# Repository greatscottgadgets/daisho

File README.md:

Daisho
======

Daisho is a SuperSpeed USB 3.0 FPGA platform.  The Daisho Platform is intended
for operation as a pair of components:

A mainboard with an FPGA can connect to a back-end computer via SuperSpeed USB.

A front-end board for a particular application connects to the mainboard via a
high speed parallel connector.

Front-end boards are planned that enable in-line monitoring and injection for
high speed wired communication media.

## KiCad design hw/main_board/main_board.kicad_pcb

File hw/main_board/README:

Copyright (c) 2013 Jared Boone, ShareBrained Technology, Inc.

These files are part of Daisho.

License
=======

This is a free hardware design; you can redistribute it and/or modify
it under the terms of the GNU General Public License as published by
the Free Software Foundation; either version 2, or (at your option)
any later version.

This design is distributed in the hope that it will be useful,
but WITHOUT ANY WARRANTY; without even the implied warranty of
MERCHANTABILITY or FITNESS FOR A PARTICULAR PURPOSE.  See the
GNU General Public License for more details.

You should have received a copy of the GNU General Public License
along with this design; see the file COPYING.  If not, write to
the Free Software Foundation, Inc., 51 Franklin Street,
Boston, MA 02110-1301, USA.

Hardware Notes
==============

Schematic and layout files were designed in KiCad (release 2012-05-21
bzr 3261 -stable), an open source electronic design automation package.

Order and type of copper layers:
    1_top: signal, front ("component" side, where most components are mounted)
    2_gnd: ground plane
    3_inner: signal
    4_gnd: ground plane
    5_pwr: power plane
    6_inner: signal
    7_gnd: ground plane
    8_bot: signal, back

PCB description: 8 layer PCB, 60 mil +/- 5% thickness
    LPI mask          0.4 mil
    Plating           1.2 mil   1.0 oz
    Copper      1     0.7 mil   0.5 oz
    Dielectric  1-2   4.4 mil   prepreg, 2 x 106-FR4 370
    Copper      2     1.2 mil   1.0 oz
    Dielectric  2-3   8.0 mil   core, FR4 370
    Copper      3     1.2 mil   1.0 oz
    Dielectric  3-4   7.8 mil   prepreg, 3 x 1080-FR4 370
    Copper      4     1.2 mil   1.0 oz
    Dielectric  4-5   8.0 mil   core, FR4 370
    Copper      5     1.2 mil   1.0 oz
    Dielectric  5-6   7.8 mil   prepreg, 3 x 1080-FR4 370
    Copper      6     1.2 mil   1.0 oz
    Dielectric  6-7   8.0 mil   core, FR4 370
    Copper      7     1.2 mil   1.0 oz
    Dielectric  7-8   4.4 mil   prepreg, 2 x 106-FR4 370
    Copper      8     0.7 mil   0.5 oz
    Plating           1.2 mil   1.0 oz
    LPI mask          0.4 mil

Impedance goals:
    50 Ohm +/- 10% microstrip, layers 1:2 at 7.0 mil (0.178 mm) width
    50 Ohm +/- 10% offset stripline, layers 3:2 at 6.5 mil (0.165 mm) width
    50 Ohm +/- 10% offset stripline, layers 6:7 at 6.5 mil (0.165 mm) width
    50 Ohm +/- 10% microstrip, layers 8:7 at 7.0 mil (0.178 mm) width

Soldermask
==========
Double side solder mask green
    +/- 5 mil solder mask registration

Silkscreen
==========
Double side silkscreen white
    6 mil silkscreen minimum width
    Silkscreen must be clipped by soldermask

Traces
======
5 mil (0.127 mm) min trace width
5 mil (0.127 mm) min trace isolation

Vias
====
8 mil (0.2032 mm) min via drill
17.7 mil (0.45 mm) min via pad
    4.85 mil min annular ring

Via-in-pad used in many places

Vias in pads need to be filled for assembly
    Most vias in pads are in capacitor footprints near the 780-BGA and 175-BGA

Drills
======
Drills are specified in two files:
    main_board.drl contains plated drills.
    main_board-NPTH.drl contains non-plated drills.

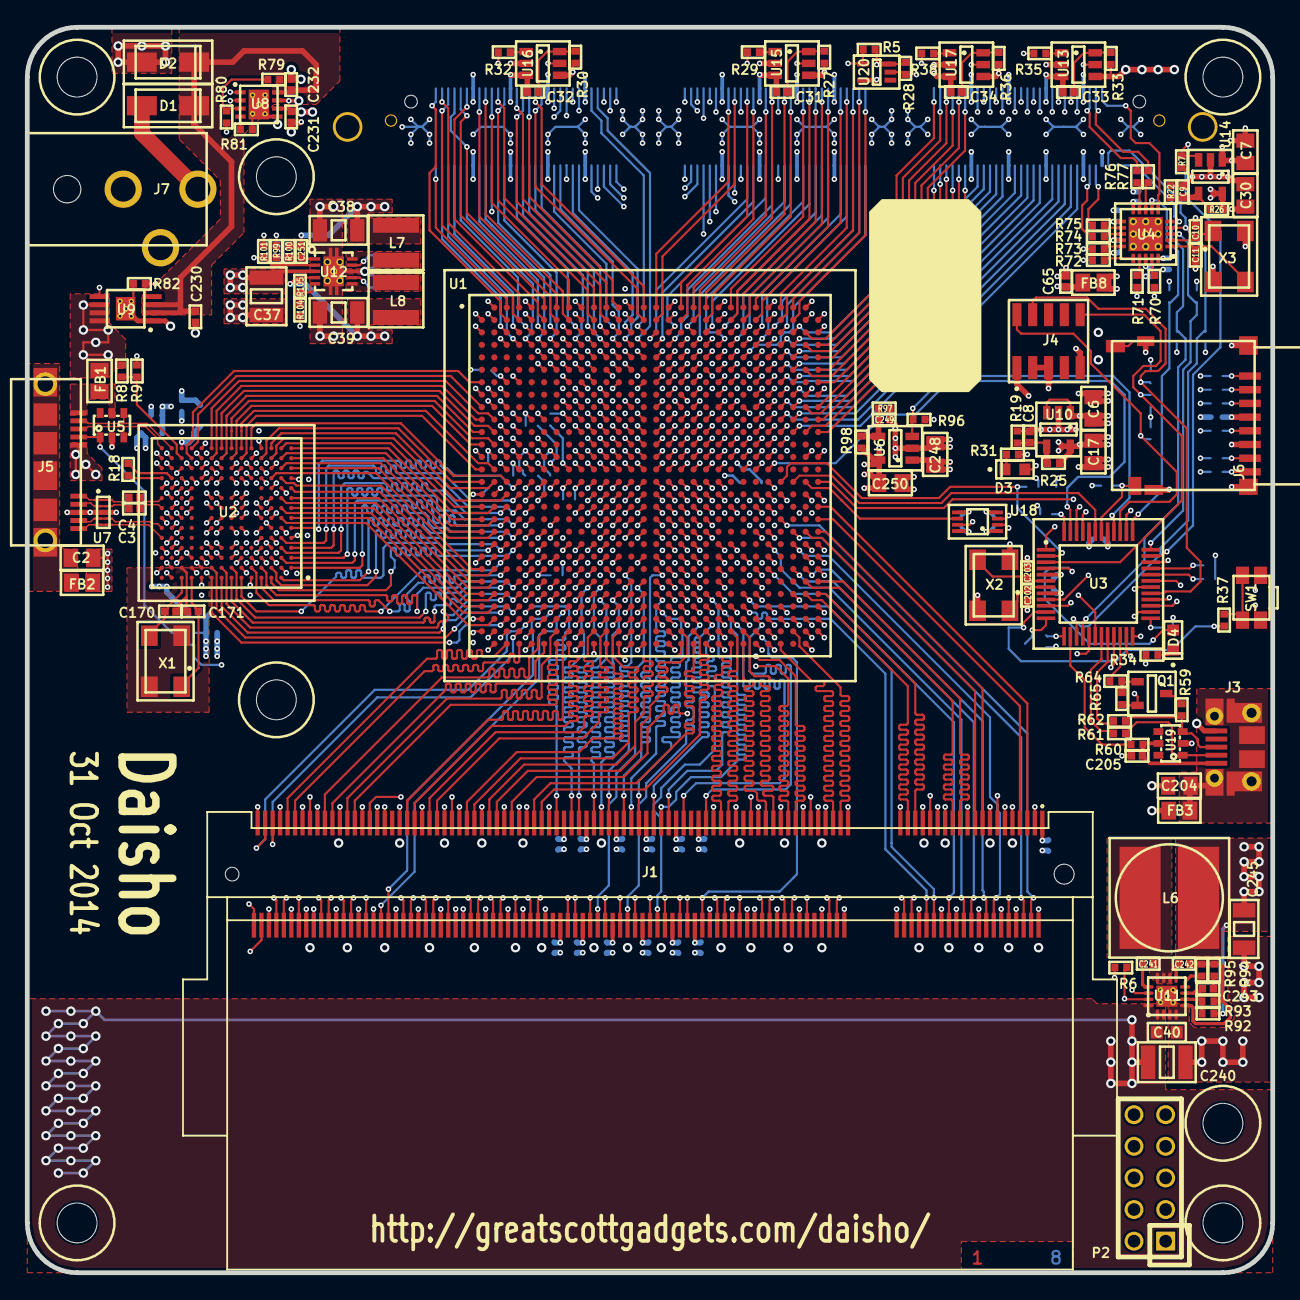
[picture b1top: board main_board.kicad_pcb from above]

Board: 8 copper layers, 100.0 x 100.0 mm, 392 parts (0 on the bottom side), 487 nets.

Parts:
C1: 1U; IPC_CAPC1005X55N
C2, C204: 10N; IPC_CAPC2012X140N
C3, C4, C5, C12, C13, C14, C15, C16, C18, C19, C20, C21, C22, C23, C24, C25, C26, C27, C28, C29, C31, C32, C33, C34, C35, C36, C41, C42, C43, C44, C45, C46, C47, C48, C49, C50, C51, C52, C53, C54, C55, C56, C57, C58, C59, C60, C61, C62, C63, C64, C65, C71, C72, C73, C74, C75, C76, C77, C78, C79, C81, C82, C83, C84, C85, C86, C87, C88, C89, C90, C91, C92, C93, C94, C95, C101, C102, C103, C104, C105, C106, C107, C108, C109, C110, C111, C112, C113, C114, C115, C116, C121, C122, C123, C124, C125, C126, C127, C128, C129, C130, C131, C132, C133, C134, C135, C141, C142, C143, C144, C145, C146, C147, C148, C149, C150, C151, C152, C153, C154, C155, C156, C160, C161, C162, C180, C181, C182, C183, C184, C185, C200, C201, C210, C211, C212, C213, C214, C215, C216, C217, C218, C219, C220, C221, C222, C230, C231, C232, C241, C4001, C4002, C4003, C4004, C4005, C4006, C4007, C4008, C4009, C4010, C4011, C4012, C4013, C4014, C4015, C4016, C4017, C4018, C4019, C4020, C4021, C4022, C4023, C4024, C4025, C4026, C4027, C4028, C4029, C4030, C4031, C4032, C4033, C4034, C4035, C4036, C4037, C4038, C4039, C4040, C4041, C4042, C4043, C4044, C4045, C4046, C4047, C4048, C4049, C4050, C4060, C4061, C4062, C4063, C4064, C4065, C4066, C4067: 100N; IPC_CAPC1005X55N
C6, C7, C17, C30, C248, C250: 10U; IPC_CAPC2012X140N
C8, C9: DNI; IPC_CAPC1005X55N
C10, C11: DNP; IPC_CAPC1005X55N
C37, C240: 22U; IPC_CAPC3225X270N
C38, C39, C245: 22U; IPC_CAPC3216X180N
C40: 100N; IPC_CAPC1608X90N
C170, C171: 27P; IPC_CAPC1005X55N
C202, C203, C251: 33P; IPC_CAPC1005X55N
C205, C242: 10N; IPC_CAPC1005X55N
C243: 2N2; IPC_CAPC1005X55N
C249: 470P; IPC_CAPC1005X55N
D1, D2: DIODESCH; IPC_DIOM5226X203N
D3, D4: LED; IPC_LEDC1608X60N
FB1, FB2, FB3, FB4, FB5, FB6, FB7, FB8: FILTER; IPC_INDC2012X130N
H1, H2, H4, H5, H6, H7, H8: HOLE; GSG-HOLE126MIL
J1: DDR2_SDRAM_SODIMM; TE_1473005-4
J2: SAMTEC_QTH-090-D; SAMTEC_QTH-090-01-F-D-A
J3: GSG-USB-MICRO-B-SHIELD; GSG-USB-MICROB-FCI-10103594
J4: CONN_5X2; SULLINS_GRPB052VWQS
J5: USB3_MICRO_AB
J6: HIROSE_DM3D
J7: BARREL_JACK; CUI_PJ-102[AB]H
L6: 2N2; TDK_VLP8040
L7, L8: 4U7; GSG-NRG4026
P1, P3: CONN_1; GSG-TESTPOINT-50MIL
P2: CONN_5X2; GSG-HEADER-2x5
Q1: BC857; IPC_SOT95P230X110-3N
R1, R2, R3, R4, R10, R11: 49R9; IPC_RESC1005X40N
R5, R7, R9, R15, R16, R17, R18, R27, R30, R33, R36, R40, R43, R44, R45, R46, R47, R48, R50, R51, R52, R53, R54, R55, R78, R82, R83, R96, R101, R102, R103: 10K; IPC_RESC1005X40N
R6, R91, R106, R107, R108, R109, R110, R111, R112: 47K; IPC_RESC1005X40N
R8: 90K9; IPC_RESC1005X40N
R12, R13, R20, R21, R23, R24, R39, R41: 1K00; IPC_RESC1005X40N
R14: 4K7; IPC_RESC1005X40N
R19, R22: 174K; IPC_RESC1005X40N
R25, R26, R98: 105K; IPC_RESC1005X40N
R28, R65: 24K; IPC_RESC1005X40N
R29, R32, R35, R37, R38, R49, R57, R58: 1K; IPC_RESC1005X40N
R31, R34: 470R; IPC_RESC1005X40N
R42: 1K0; IPC_RESC1005X40N
R59: 1K5; IPC_RESC1005X40N
R60: 100R; IPC_RESC1005X40N
R61, R62: 33R; IPC_RESC1005X40N
R64: 3K; IPC_RESC1005X40N
R70, R71, R72, R73, R74, R75, R76, R77: 10R; IPC_RESC1005X40N
R79: 47K0; IPC_RESC1005X40N
R80, R93: 10K0; IPC_RESC1005X40N
R81: 249R; IPC_RESC1005X40N
R92: 12K7; IPC_RESC1005X40N
R94: 6K34; IPC_RESC1005X40N
R95: 158K; IPC_RESC1005X40N
R97: 107K; IPC_RESC1005X40N
R99, R100: 100K; IPC_RESC1005X40N
R104: 165K; IPC_RESC1005X40N
R105: 137K; IPC_RESC1005X40N
SW1: SW_PUSH; PANASONIC_EVQP7_A_C_J_L
U1: EP4CE30F29; IPC_BGA780C100P28X28_2900X2900X350
U2: TUSB1310A; IPC_BGA175C80P14X14_1200X1200X140
U3: LPC11U1X; IPC_QFP50P900X900X160-48N
U4: SI5351C-B; IPC_QFN50P400X400X90-21L
U5, U19: GSG-IP4220CZ6; GSG-SOT457
U6, U10, U14: MIC5207YM5; IPC_SOT95P280X110-5N
U7: USB3_ESD_SON50-10
U8: TPS2113A; TI_DRB_S-PVSON-N8
U9: TPS2065C-2; TI_DGN_S-PDSO-G8
U11: TPS54218; TI_RTE_S-PWQFN-N16
U12: TPS62420; TI_DRC_S-PVSON-N10
U13, U15, U16, U17: TPS27081A; IPC_SOT95P280X110-6N
U18: 74LVC2T45; IPC_SOP50P310X100-8N
U20: INV1; IPC_SOT65P210X110-5N
X1: 40M; IPC_OSCCC320X500X105-4N
X2: 12M; IPC_OSCCC320X500X105-4N
X3: 25M; IPC_OSCCC320X500X105-4N

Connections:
/clock_generator/CLOCKGEN_INTR#: R14.2, U3.36, U4.3
/clock_generator/CLOCKGEN_OEB#: R15.2, U3.37, U4.7
/clock_generator/FE_CLKSRC: J2.5, U4.6
/clock_generator/FE_CLK_N0: J2.10, R74.2
/clock_generator/FE_CLK_N1: J2.9, R76.2
/clock_generator/FE_CLK_P0: J2.8, R75.2
/clock_generator/FE_CLK_P1: J2.7, R77.2
/clock_generator/V1P8A: C14.1, C15.1, FB8.2, U4.14, U4.18
/ddr2/A0: J1.102, U1.AE13
/ddr2/A1: J1.101, U1.AB15
/ddr2/A2: J1.100, U1.AF18
/ddr2/A3: J1.99, U1.AD15
/ddr2/A4: J1.98, U1.AF14
/ddr2/A5: J1.97, U1.AE15
/ddr2/A6: J1.94, U1.AE14
/ddr2/A7: J1.92, U1.AG19
/ddr2/A8: J1.93, U1.AF19
/ddr2/A9: J1.91, U1.AE20
/ddr2/A10: J1.105, U1.AB13
/ddr2/A11: J1.90, U1.AD14
/ddr2/A12: J1.89, U1.AD19
/ddr2/A13: J1.116, U1.AH10
/ddr2/A14: J1.86, U1.AC17
/ddr2/A15: J1.84, U1.AE16
/ddr2/BA0: J1.107, U1.AD12
/ddr2/BA1: J1.106, U1.AH12
/ddr2/BA2: J1.85, U1.AF21
/ddr2/CAS#: J1.113, U1.AC11
/ddr2/CK0: J1.30, U1.AD22
/ddr2/CK1: J1.164, U1.AE7
/ddr2/CK#0: J1.32, U1.AE22
/ddr2/CK#1: J1.166, U1.AE8
/ddr2/CKE0: J1.79, U1.AF23
/ddr2/CKE1: J1.80, U1.AG23
/ddr2/DM0: J1.10, U1.AB28
/ddr2/DM1: J1.26, U1.AB24
/ddr2/DM2: J1.52, U1.AF25
/ddr2/DM3: J1.67, U1.AH19
/ddr2/DM4: J1.130, U1.AC15
/ddr2/DM5: J1.147, U1.AF8
/ddr2/DM6: J1.170, U1.AB9
/ddr2/DM7: J1.185, U1.AE6
/ddr2/DQ0: J1.5, U1.U28
/ddr2/DQ1: J1.7, U1.V28
/ddr2/DQ2: J1.17, U1.W28
/ddr2/DQ3: J1.19, U1.W27
/ddr2/DQ4: J1.4, U1.V25
/ddr2/DQ5: J1.6, U1.W26
/ddr2/DQ6: J1.14, U1.Y26
/ddr2/DQ7: J1.16, U1.AB27
/ddr2/DQ8: J1.23, U1.AC28
/ddr2/DQ9: J1.25, U1.AC27
/ddr2/DQ10: J1.35, U1.AD28
/ddr2/DQ11: J1.37, U1.AD27
/ddr2/DQ12: J1.20, U1.AB26
/ddr2/DQ13: J1.22, U1.Y24
/ddr2/DQ14: J1.36, U1.AD26
/ddr2/DQ15: J1.38, U1.AE28
/ddr2/DQ16: J1.43, U1.AG26
/ddr2/DQ17: J1.45, U1.AH25
/ddr2/DQ18: J1.55, U1.AF22
/ddr2/DQ19: J1.57, U1.AE21
/ddr2/DQ20: J1.44, U1.AE25
/ddr2/DQ21: J1.46, U1.AE24
/ddr2/DQ22: J1.56, U1.AF20
/ddr2/DQ23: J1.58, U1.AD18
/ddr2/DQ24: J1.61, U1.AG22
/ddr2/DQ25: J1.63, U1.AH22
/ddr2/DQ26: J1.73, U1.AG21
/ddr2/DQ27: J1.75, U1.AH21
/ddr2/DQ28: J1.62, U1.AF24
/ddr2/DQ29: J1.64, U1.AH23
/ddr2/DQ30: J1.74, U1.AE19
/ddr2/DQ31: J1.76, U1.AD17
/ddr2/DQ32: J1.123, U1.AG18
/ddr2/DQ33: J1.125, U1.AH18
/ddr2/DQ34: J1.135, U1.AG17
/ddr2/DQ35: J1.137, U1.AH17
/ddr2/DQ36: J1.124, U1.AE17
/ddr2/DQ37: J1.126, U1.AF16
/ddr2/DQ38: J1.134, U1.AF15
/ddr2/DQ39: J1.136, U1.AB16
/ddr2/DQ40: J1.141, U1.AG12
/ddr2/DQ41: J1.143, U1.AH11
/ddr2/DQ42: J1.151, U1.AG11
/ddr2/DQ43: J1.153, U1.AG10
/ddr2/DQ44: J1.140, U1.AE12
/ddr2/DQ45: J1.142, U1.AE11
/ddr2/DQ46: J1.152, U1.AE9
/ddr2/DQ47: J1.154, U1.AF10
/ddr2/DQ48: J1.157, U1.AH8
/ddr2/DQ49: J1.159, U1.AG8
/ddr2/DQ50: J1.173, U1.AH7
/ddr2/DQ51: J1.175, U1.AG7
/ddr2/DQ52: J1.158, U1.AF9
/ddr2/DQ53: J1.160, U1.AD10
/ddr2/DQ54: J1.174, U1.AC8
/ddr2/DQ55: J1.176, U1.AF7
/ddr2/DQ56: J1.179, U1.AH6
/ddr2/DQ57: J1.181, U1.AG6
/ddr2/DQ58: J1.189, U1.AH4
/ddr2/DQ59: J1.191, U1.AH3
/ddr2/DQ60: J1.180, U1.AD8
/ddr2/DQ61: J1.182, U1.AF6
/ddr2/DQ62: J1.192, U1.AF4
/ddr2/DQ63: J1.194, U1.AG3
/ddr2/DQS0: J1.13, U1.T25
/ddr2/DQS1: J1.31, U1.AF27
/ddr2/DQS2: J1.51, U1.AF26
/ddr2/DQS3: J1.70, U1.AE18
/ddr2/DQS4: J1.131, U1.AF17
/ddr2/DQS5: J1.148, U1.AF11
/ddr2/DQS6: J1.169, U1.AE10
/ddr2/DQS7: J1.188, U1.AD7
/ddr2/ODT0: J1.114, U1.AF12
/ddr2/ODT1: J1.119, U1.AE5
/ddr2/RAS#: J1.108, U1.AC14
/ddr2/S#0: J1.110, U1.AF13
/ddr2/S#1: J1.115, U1.AC10
/ddr2/VREF: C180.2, C181.1, C182.2, C183.1, C184.2, C185.1, C222.1, J1.1, R20.2, R21.1, U1.AA12, U1.AA14, U1.AA15, U1.AA24, U1.AB11, U1.AB20, U1.AC18, U1.R24, U1.U23, U1.U24, U1.Y10, U1.Y17
/ddr2/WE#: J1.109, U1.AD11
/fpga_configuration/DATA0: R47.1, U1.N7
/fpga_configuration/DCLK: R46.1, U1.P3
/fpga_configuration/FPGA_NSTATUS: R50.2, U1.M6, U3.48
/fpga_configuration/FPGA_TCK: P2.1, R49.1, U1.P5, U3.13
/fpga_configuration/FPGA_TDI: P2.9, R44.2, U1.P7, U3.17
/fpga_configuration/FPGA_TDO_V1P8: U1.P6, U18.7
/fpga_configuration/FPGA_TMS: P2.5, R45.2, U1.P8, U3.18
/fpga_configuration/NCE: R48.1, U1.R8
/fpga_configuration/NCONFIG: R43.2, U1.P4
/fpga_configuration/PIPE_RATE: U1.N3, U2.L6
/fpga_configuration/PIPE_TX_DETRX_LPBK: U1.K4, U2.M6
/fpga_configuration/PIPE_TX_ELECIDLE: U1.M4, U2.K3
/fpga_configuration/PIPE_TX_MARGIN0: U1.K3, U2.M9
/fpga_configuration/PIPE_TX_MARGIN1: U1.H3, U2.M10
/fpga_configuration/PIPE_TX_MARGIN2: U1.G4, U2.M11
/fpga_configuration/PIPE_TX_ONESZEROS: U1.M3, U2.M4
/fpga_configuration/PIPE_TX_SWING: U1.L4, U2.M5
/fpga_configuration/ULPI_CLK: U1.J1, U2.P11
/fpga_configuration/ULPI_DATA0: U1.K1, U2.N9
/fpga_configuration/ULPI_DATA1: U1.K2, U2.P9
/fpga_configuration/ULPI_DATA2: U1.L2, U2.P8
/fpga_configuration/ULPI_DATA3: U1.L1, U2.N8
/fpga_configuration/ULPI_DATA4: U1.M2, U2.P7
/fpga_configuration/ULPI_DATA5: U1.M1, U2.N7
/fpga_configuration/ULPI_DATA6: U1.P2, U2.P6
/fpga_configuration/ULPI_DATA7: U1.P1, U2.N6
/fpga_configuration/ULPI_DIR: U1.L3, U2.M7
/fpga_configuration/ULPI_NXT: U1.G1, U2.N11
/fpga_configuration/ULPI_STP: U1.J3, U2.M8
/fpga_ddr2/CLK_N0: R72.2, U1.AH14
/fpga_ddr2/CLK_N1: R70.2, U1.Y28
/fpga_ddr2/CLK_P0: R73.2, U1.AG14
/fpga_ddr2/CLK_P1: R71.2, U1.Y27
/fpga_ddr2/SPI_MISO_V1P8: U1.R27, U18.6
/fpga_ddr2/SPI_MOSI: U1.R28, U3.38
/fpga_ddr2/SPI_SCK: U1.R26, U3.43
/fpga_ddr2/SPI_SS: R52.2, U1.R25, U3.2
/fpga_front_end_bank_b/D0: J2.62, U1.E22
/fpga_front_end_bank_b/D1: J2.61, U1.B26
/fpga_front_end_bank_b/D2: J2.64, U1.C25
/fpga_front_end_bank_b/D3: J2.63, U1.A26
/fpga_front_end_bank_b/D4: J2.66, U1.C24
/fpga_front_end_bank_b/D5: J2.65, U1.B25
/fpga_front_end_bank_b/D6: J2.68, U1.D23
/fpga_front_end_bank_b/D7: J2.67, U1.A25
/fpga_front_end_bank_b/D8: J2.70, U1.C23
/fpga_front_end_bank_b/D9: J2.69, U1.B23
/fpga_front_end_bank_b/D10: J2.74, U1.C22
/fpga_front_end_bank_b/D11: J2.73, U1.A23
/fpga_front_end_bank_b/D12: J2.76, U1.D21
/fpga_front_end_bank_b/D13: J2.75, U1.B22
/fpga_front_end_bank_b/D14: J2.78, U1.C20
/fpga_front_end_bank_b/D15: J2.77, U1.A22
/fpga_front_end_bank_b/D16: J2.80, U1.C19
/fpga_front_end_bank_b/D17: J2.79, U1.B21
/fpga_front_end_bank_b/D18: J2.82, U1.D20
/fpga_front_end_bank_b/D19: J2.81, U1.A21
/fpga_front_end_bank_b/D20: J2.86, U1.D18
/fpga_front_end_bank_b/D21: J2.85, U1.B19
/fpga_front_end_bank_b/D22: J2.88, U1.C18
/fpga_front_end_bank_b/D23: J2.87, U1.A19
/fpga_front_end_bank_b/D24: J2.90, U1.G21
/fpga_front_end_bank_b/D25: J2.89, U1.D22
/fpga_front_end_bank_b/D26: J2.92, U1.D16
/fpga_front_end_bank_b/D27: J2.91, U1.B18
/fpga_front_end_bank_b/D28: J2.94, U1.C16
/fpga_front_end_bank_b/D29: J2.93, U1.A18
/fpga_front_end_bank_b/D30: J2.98, U1.D15
/fpga_front_end_bank_b/D31: J2.97, U1.B17
/fpga_front_end_bank_b/D32: J2.100, U1.C15
/fpga_front_end_bank_b/D33: J2.99, U1.A17
/fpga_front_end_bank_b/D34: J2.102, U1.G20
/fpga_front_end_bank_b/D35: J2.101, U1.E18
/fpga_front_end_bank_b/D36: J2.104, U1.D19
/fpga_front_end_bank_b/D37: J2.103, U1.B15
/fpga_front_end_bank_b/D38: J2.106, U1.C21
/fpga_front_end_bank_b/D39: J2.105, U1.A15
/fpga_front_end_bank_b/D40: J2.110, U1.F21
/fpga_front_end_bank_b/D41: J2.109, U1.D17
/fpga_front_end_bank_b/D42: J2.112, U1.E21
/fpga_front_end_bank_b/D43: J2.111, U1.F17
/fpga_front_end_bank_b/D44: J2.114, U1.H17
/fpga_front_end_bank_b/D45: J2.113, U1.G18
/fpga_front_end_bank_b/D46: J2.116, U1.H16
/fpga_front_end_bank_b/D47: J2.115, U1.F15
/fpga_front_end_bank_b/D48: J2.118, U1.J17
/fpga_front_end_bank_b/D49: J2.117, U1.G16
/fpga_front_end_bank_b/D50: J2.120, U1.E17
/fpga_front_end_bank_b/D51: J2.119, U1.E15
/fpga_front_end_bank_b/VCCIO_DEFAULT_EN: R5.1, U15.5, U16.5, U17.5, U20.4
/fpga_front_end_bank_b/VREF: C19.2, C23.1, R12.1, R13.2, U1.F18, U1.F22, U1.G15, U1.G17
/fpga_front_end_bank_c/D0: J2.122, U1.E8
/fpga_front_end_bank_c/D1: J2.121, U1.F12
/fpga_front_end_bank_c/D2: J2.124, U1.E11
/fpga_front_end_bank_c/D3: J2.123, U1.E12
/fpga_front_end_bank_c/D4: J2.126, U1.E14
/fpga_front_end_bank_c/D5: J2.125, U1.C8
/fpga_front_end_bank_c/D6: J2.128, U1.E7
/fpga_front_end_bank_c/D7: J2.127, U1.D14
/fpga_front_end_bank_c/D8: J2.130, U1.E10
/fpga_front_end_bank_c/D9: J2.129, U1.C14
/fpga_front_end_bank_c/D10: J2.134, U1.D13
/fpga_front_end_bank_c/D11: J2.133, U1.F10
/fpga_front_end_bank_c/D12: J2.136, U1.C13
/fpga_front_end_bank_c/D13: J2.135, U1.D10
/fpga_front_end_bank_c/D14: J2.138, U1.G10
/fpga_front_end_bank_c/D15: J2.137, U1.D8
/fpga_front_end_bank_c/D16: J2.140, U1.D12
/fpga_front_end_bank_c/D17: J2.139, U1.F7
/fpga_front_end_bank_c/D18: J2.142, U1.C12
/fpga_front_end_bank_c/D19: J2.141, U1.F8
/fpga_front_end_bank_c/D20: J2.146, U1.C11
/fpga_front_end_bank_c/D21: J2.145, U1.B14
/fpga_front_end_bank_c/D22: J2.148, U1.D11
/fpga_front_end_bank_c/D23: J2.147, U1.A14
/fpga_front_end_bank_c/D24: J2.150, U1.C10
/fpga_front_end_bank_c/D25: J2.149, U1.A12
/fpga_front_end_bank_c/D26: J2.152, U1.D9
/fpga_front_end_bank_c/D27: J2.151, U1.B11
/fpga_front_end_bank_c/D28: J2.154, U1.C9
/fpga_front_end_bank_c/D29: J2.153, U1.A11
/fpga_front_end_bank_c/D30: J2.158, U1.D7
/fpga_front_end_bank_c/D31: J2.157, U1.B10
/fpga_front_end_bank_c/D32: J2.160, U1.C7
/fpga_front_end_bank_c/D33: J2.159, U1.A10
/fpga_front_end_bank_c/D34: J2.162, U1.G8
/fpga_front_end_bank_c/D35: J2.161, U1.A8
/fpga_front_end_bank_c/D36: J2.164, U1.D6
/fpga_front_end_bank_c/D37: J2.163, U1.B8
/fpga_front_end_bank_c/D38: J2.166, U1.C6
/fpga_front_end_bank_c/D39: J2.165, U1.A7
/fpga_front_end_bank_c/D40: J2.170, U1.D5
/fpga_front_end_bank_c/D41: J2.169, U1.B6
/fpga_front_end_bank_c/D42: J2.172, U1.C5
/fpga_front_end_bank_c/D43: J2.171, U1.A6
/fpga_front_end_bank_c/D44: J2.174, U1.C4
/fpga_front_end_bank_c/D45: J2.173, U1.B7
/fpga_front_end_bank_c/D46: J2.176, U1.D4
/fpga_front_end_bank_c/D47: J2.175, U1.B4
/fpga_front_end_bank_c/D48: J2.178, U1.C3
/fpga_front_end_bank_c/D49: J2.177, U1.A4
/fpga_front_end_bank_c/D50: J2.180, U1.A3
/fpga_front_end_bank_c/D51: J2.179, U1.B3
/fpga_front_end_bank_c/VREF: C20.2, C22.1, R41.2, R42.1, U1.F11, U1.G9, U1.G12, U1.G14
/fpga_front_end_misc/D0: J2.14, U1.L26
/fpga_front_end_misc/D1: J2.13, U1.M23
/fpga_front_end_misc/D2: J2.16, U1.K25
/fpga_front_end_misc/D3: J2.15, U1.L23
/fpga_front_end_misc/D4: J2.18, U1.K26
/fpga_front_end_misc/D5: J2.17, U1.J23
/fpga_front_end_misc/D6: J2.20, U1.J25
/fpga_front_end_misc/D7: J2.19, U1.H23
/fpga_front_end_misc/D8: J2.22, U1.J26
/fpga_front_end_misc/D9: J2.21, U1.G23
/fpga_front_end_misc/D10: J2.26, U1.H26
/fpga_front_end_misc/D11: J2.25, U1.M24
/fpga_front_end_misc/D12: J2.28, U1.G25
/fpga_front_end_misc/D13: J2.27, U1.L25
/fpga_front_end_misc/D14: J2.30, U1.G26
/fpga_front_end_misc/D15: J2.29, U1.L24
/fpga_front_end_misc/D16: J2.32, U1.F25
/fpga_front_end_misc/D17: J2.31, U1.J24
/fpga_front_end_misc/D18: J2.34, U1.F26
/fpga_front_end_misc/D19: J2.33, U1.H25
/fpga_front_end_misc/D20: J2.38, U1.E25
/fpga_front_end_misc/D21: J2.37, U1.H24
/fpga_front_end_misc/D22: J2.40, U1.E26
/fpga_front_end_misc/D23: J2.39, U1.G24
/fpga_front_end_misc/D24: J2.42, U1.D25
/fpga_front_end_misc/D25: J2.41, U1.F24
/fpga_front_end_misc/D26: J2.44, U1.D26
/fpga_front_end_misc/D27: J2.43, U1.E24
/fpga_front_end_misc/D28: J2.46, U1.C26
/fpga_front_end_misc/D29: J2.45, U1.D24
/fpga_front_end_misc/D30: J2.50, U1.L28
/fpga_front_end_misc/D31: J2.49, U1.F27
/fpga_front_end_misc/D32: J2.52, U1.L27
/fpga_front_end_misc/D33: J2.51, U1.F28
/fpga_front_end_misc/D34: J2.54, U1.K28
/fpga_front_end_misc/D35: J2.53, U1.E28
/fpga_front_end_misc/D36: J2.56, U1.J27
/fpga_front_end_misc/D37: J2.55, U1.D27
/fpga_front_end_misc/D38: J2.58, U1.J28
/fpga_front_end_misc/D39: J2.57, U1.D28
/fpga_front_end_misc/D40: J2.60, U1.G28
/fpga_front_end_misc/D41: J2.59, U1.C27
/fpga_front_end_misc/FPGA_CONF_DONE: R51.2, U1.P24, U3.47
/fpga_front_end_misc/VREF: C18.2, C21.1, R23.1, R24.2, U1.J22, U1.M21, U1.M25, U1.N21
/fpga_power/VCCD_PLL: C4064.1, C4065.1, C4066.1, C4067.1, FB7.2, U1.J9, U1.J20, U1.Y9, U1.Y20
/fpga_usb0/PIPE_POWERDOWN0: U1.R7, U2.H3
/fpga_usb0/PIPE_POWERDOWN1: U1.R5, U2.G3
/fpga_usb0/PIPE_PWRPRESENT: U1.AB5, U2.H11
/fpga_usb0/PIPE_RESETN: R16.2, U1.AB6, U2.J11
/fpga_usb0/PIPE_RX_DATA0: U1.T4, U2.E2
/fpga_usb0/PIPE_RX_DATA1: U1.U3, U2.D2
/fpga_usb0/PIPE_RX_DATA2: U1.U4, U2.D1
/fpga_usb0/PIPE_RX_DATA3: U1.V4, U2.C1
/fpga_usb0/PIPE_RX_DATA4: U1.V3, U2.C2
/fpga_usb0/PIPE_RX_DATA5: U1.W4, U2.B1
/fpga_usb0/PIPE_RX_DATA6: U1.W3, U2.A2
/fpga_usb0/PIPE_RX_DATA7: U1.Y4, U2.A3
/fpga_usb0/PIPE_RX_DATA8: U1.Y3, U2.B3
/fpga_usb0/PIPE_RX_DATA9: U1.AB3, U2.A4
/fpga_usb0/PIPE_RX_DATA10: U1.AC4, U2.B4
/fpga_usb0/PIPE_RX_DATA11: U1.AA3, U2.B5
/fpga_usb0/PIPE_RX_DATA12: U1.AD3, U2.B8
/fpga_usb0/PIPE_RX_DATA13: U1.AE4, U2.A8
/fpga_usb0/PIPE_RX_DATA14: U1.AF3, U2.A9
/fpga_usb0/PIPE_RX_DATA15: U1.AE3, U2.B9
/fpga_usb0/PIPE_RX_DATAK0: U1.AD4, U2.A7
/fpga_usb0/PIPE_RX_DATAK1: U1.AC3, U2.B7
/fpga_usb0/PIPE_RX_ELECIDLE: U1.R6, U2.F3
/fpga_usb0/PIPE_RX_POLARITY: U1.AC5, U2.C8
/fpga_usb0/PIPE_RX_STATUS0: U1.V7, U2.C5
/fpga_usb0/PIPE_RX_STATUS1: U1.Y6, U2.C6
/fpga_usb0/PIPE_RX_STATUS2: U1.AA6, U2.C7
/fpga_usb0/PIPE_RX_TERMINATION: U1.U5, U2.D3
/fpga_usb0/PIPE_RX_VALID: U1.R4, U2.F1
/fpga_usb0/PIPE_TX_CLK: U1.AC1, U2.K1
/fpga_usb0/PIPE_TX_DATA0: U1.R3, U2.P5
/fpga_usb0/PIPE_TX_DATA1: U1.R1, U2.N4
/fpga_usb0/PIPE_TX_DATA2: U1.R2, U2.P3
/fpga_usb0/PIPE_TX_DATA3: U1.T3, U2.N3
/fpga_usb0/PIPE_TX_DATA4: U1.U1, U2.P2
/fpga_usb0/PIPE_TX_DATA5: U1.V1, U2.N2
/fpga_usb0/PIPE_TX_DATA6: U1.U2, U2.P1
/fpga_usb0/PIPE_TX_DATA7: U1.V2, U2.N1
/fpga_usb0/PIPE_TX_DATA8: U1.W2, U2.M1
/fpga_usb0/PIPE_TX_DATA9: U1.W1, U2.M2
/fpga_usb0/PIPE_TX_DATA10: U1.AB2, U2.L2
/fpga_usb0/PIPE_TX_DATA11: U1.AB1, U2.L3
/fpga_usb0/PIPE_TX_DATA12: U1.AD1, U2.J2
/fpga_usb0/PIPE_TX_DATA13: U1.AD2, U2.H1
/fpga_usb0/PIPE_TX_DATA14: U1.AE1, U2.H2
/fpga_usb0/PIPE_TX_DATA15: U1.AF2, U2.G2
/fpga_usb0/PIPE_TX_DATAK0: U1.AC2, U2.J1
/fpga_usb0/PIPE_TX_DATAK1: U1.AE2, U2.G1
/fpga_usb0/PIPE_TX_DEEMPH0: U1.AA5, U2.L11
/fpga_usb0/PIPE_TX_DEEMPH1: U1.AA7, U2.K11
/fpga_usb0/USB3_ID: J5.4, R39.2, U5.1
/front_end/FE_EN: U3.9, U13.5
/front_end/FE_I2C_SCL: J1.197, J2.4, R57.2, U1.AF5, U3.15, U4.4
/front_end/FE_I2C_SDA: J1.195, J2.2, R58.2, U1.AG4, U3.16, U4.5
/front_end/FE_VCCIO_A: C18.1, C34.2, C90.1, C91.1, C92.1, C93.1, C94.1, C95.1, J2.12, J2.24, J2.36, J2.48, R23.2, U1.B28, U1.H28, U1.K24, U1.L21, U1.N24, U1.N28, U17.2, U17.3
/front_end/FE_VCCIO_B: C19.1, C31.2, C81.1, C82.1, C83.1, C84.1, C85.1, C86.1, C87.1, C88.1, C89.1, J2.71, J2.72, J2.83, J2.84, J2.95, J2.96, J2.107, J2.108, R10.2, R12.2, U1.A16, U1.A20, U1.A24, U1.A27, U1.E16, U1.E20, U1.E23, U1.H18, U1.J15, U15.2, U15.3
/front_end/FE_VCCIO_C: C20.1, C32.2, C71.1, C72.1, C73.1, C74.1, C75.1, C76.1, C77.1, C78.1, C79.1, J2.131, J2.132, J2.143, J2.144, J2.155, J2.156, J2.167, J2.168, R41.1, U1.A2, U1.A5, U1.A9, U1.A13, U1.E6, U1.E9, U1.E13, U1.H11, U1.J13, U16.2, U16.3
/front_end/VRAW_SW: C33.2, J2.11, J2.23, J2.35, J2.47, U13.2, U13.3
/microcontroller/ALT_SW_STAT: R78.1, U3.32, U8.1
/microcontroller/DDR2_SA0: J1.198, U3.21
/microcontroller/DDR2_SA1: J1.200, U3.23
/microcontroller/FPGA_MISO_V3P3: U3.30, U18.3
/microcontroller/FPGA_TDO_V3P3: P2.3, U3.26, U18.2
/microcontroller/LED_STATUS: D4.1, U3.4
/microcontroller/RESET#: J4.10, R54.2, U3.3
/microcontroller/RXD: P1.1, R37.1, U3.11
/microcontroller/SD_CS#: J6.2, R109.2, U3.10
/microcontroller/SD_DET: J6.A, R106.2, U3.42
/microcontroller/SD_MISO: J6.7, R107.2, U3.27
/microcontroller/SD_MOSI: J6.3, R108.2, U3.28
/microcontroller/SD_SCK: J6.5, R112.1, U3.31
/microcontroller/SWCLK: J4.4, R55.1, U3.29
/microcontroller/SWDIO: J4.2, R53.2, U3.39
/microcontroller/TXD: P3.1, U3.12
/microcontroller/USB2_SHIELD: C204.1, FB3.2, J3.6
/microcontroller/USB_POWER_EN: R82.2, U3.34, U9.4
/microcontroller/USB_POWER_FLT#: R83.1, U3.33, U9.5
/microcontroller/V1P8_PWRGD: R91.2, U3.25, U11.14
/microcontroller/V1PX_SMPS_MODE: R101.2, U3.1, U12.2
/power/V1P1_EN: R103.2, U3.45, U12.7
/power/V1P1_FB: R104.1, R105.2, U12.5
/power/V1P1_SW: L8.1, U12.6
/power/V1P2_EN: R102.2, U3.46, U12.9
/power/V1P2_FB: C251.1, R99.1, R100.2, U12.1
/power/V1P2_SW: L7.2, U12.10
/power/V1P8_EN: R6.2, U3.24, U11.15
/power/V1P8_PH: C241.2, L6.1, U11.10, U11.11, U11.12
/power/V2P5_EN: R96.2, U3.40, U6.3
/power/V3P3A_EN: R7.2, U3.35, U14.3
/power/VALT: C230.1, C232.1, D1.2, D2.2, R79.2, U8.8, U9.2, U9.3
/usb0_interfaces/DM: J5.2, U2.P13, U5.4
/usb0_interfaces/DP: J5.3, U2.P14, U5.3
/usb0_interfaces/ELAS_BUF_MODE: U1.AD5, U2.C9
/usb0_interfaces/OUT_ENABLE: R17.2, U1.G3, U2.L10
/usb0_interfaces/PCLK: U1.Y2, U2.A6
/usb0_interfaces/PHY_RESETN: U1.N4, U2.J3
/usb0_interfaces/PHY_STATUS: U1.V5, U2.E3
/usb0_interfaces/SSRXM: J5.9, U2.F14, U7.4
/usb0_interfaces/SSRXP: J5.10, U2.E14, U7.5
/usb0_interfaces/SSTXM: C4.1, U2.J14
/usb0_interfaces/SSTXM_C: C4.2, J5.6, U7.1
/usb0_interfaces/SSTXP: C3.1, U2.H14
/usb0_interfaces/SSTXP_C: C3.2, J5.7, U7.2
/usb0_interfaces/USB3_SHIELD: C2.1, FB2.2, J5.11
/usb0_interfaces/VBUS: R8.1, R9.2, U2.N12
/usb0_interfaces/VSSOSC: C170.2, C171.2, U2.B12, X1.2, X1.4
/usb0_interfaces/VUSB_RAW: FB1.1, J5.1, U5.5
/usb0_interfaces/XI: C170.1, U2.A12, X1.3
/usb0_interfaces/XO: C171.1, U2.A11, X1.1
/usb0_power/A1P1: C1.1, C145.1, C146.1, C147.1, C148.1, C149.1, C150.1, FB6.2, U2.C11, U2.C12, U2.D14, U2.G13, U2.G14, U2.K14, U2.M14
/usb0_power/A1P8: C142.1, C143.1, C144.1, FB5.2, U2.A13, U2.C10, U2.N14
/usb0_power/A3P3: C141.1, FB4.2, U2.P12
GND: C1.2, C2.2, C5.2, C6.2, C7.2, C8.2, C9.2, C10.1, C11.2, C12.2, C13.2, C14.2, C15.2, C16.2, C17.2, C21.2, C22.2, C23.2, C24.2, C25.2, C26.2, C27.2, C28.2, C29.2, C30.2, C35.1, C36.1, C37.2, C38.2, C39.1, C40.2, C41.2, C42.2, C43.2, C44.2, C45.2, C46.2, C47.2, C48.2, C49.2, C50.2, C51.2, C52.2, C53.2, C54.2, C55.2, C56.2, C57.2, C58.2, C59.2, C60.2, C61.2, C62.2, C63.2, C64.2, C65.2, C71.2, C72.2, C73.2, C74.2, C75.2, C76.2, C77.2, C78.2, C79.2, C81.2, C82.2, C83.2, C84.2, C85.2, C86.2, C87.2, C88.2, C89.2, C90.2, C91.2, C92.2, C93.2, C94.2, C95.2, C101.2, C102.2, C103.2, C104.2, C105.2, C106.2, C107.2, C108.2, C109.2, C110.2, C111.2, C112.2, C113.2, C114.2, C115.2, C116.2, C121.2, C122.2, C123.2, C124.2, C125.2, C126.2, C127.2, C128.2, C129.2, C130.2, C131.2, C132.2, C133.2, C134.2, C135.2, C141.2, C142.2, C143.2, C144.2, C145.2, C146.2, C147.2, C148.2, C149.2, C150.2, C151.2, C152.2, C153.2, C154.2, C155.2, C156.2, C160.2, C161.2, C162.2, C181.2, C183.2, C185.2, C200.2, C201.2, C202.1, C203.2, C204.2, C205.2, C210.2, C211.2, C212.2, C213.2, C214.2, C215.2, C216.2, C217.2, C218.2, C219.2, C220.2, C221.2, C222.2, C230.2, C231.2, C232.2, C240.2, C242.2, C245.2, C248.2, C249.2, C250.2, C4001.2, C4002.2, C4003.2, C4004.2, C4005.2, C4006.2, C4007.2, C4008.2, C4009.2, C4010.2, C4011.2, C4012.2, C4013.2, C4014.2, C4015.2, C4016.2, C4017.2, C4018.2, C4019.2, C4020.2, C4021.2, C4022.2, C4023.2, C4024.2, C4025.2, C4026.2, C4027.2, C4028.2, C4029.2, C4030.2, C4031.2, C4032.2, C4033.2, C4034.2, C4035.2, C4036.2, C4037.2, C4038.2, C4039.2, C4040.2, C4041.2, C4042.2, C4043.2, C4044.2, C4045.2, C4046.2, C4047.2, C4048.2, C4049.2, C4050.2, C4060.2, C4061.2, C4062.2, C4063.2, C4064.2, C4065.2, C4066.2, C4067.2, FB2.1, FB3.1, J1.2, J1.3, J1.8, J1.9, J1.11, J1.12, J1.15, J1.18, J1.21, J1.24, J1.27, J1.28, J1.29, J1.33, J1.34, J1.39, J1.40, J1.41, J1.42, J1.47, J1.48, J1.49, J1.53, J1.54, J1.59, J1.60, J1.65, J1.66, J1.68, J1.71, J1.72, J1.77, J1.78, J1.121, J1.122, J1.127, J1.128, J1.129, J1.132, J1.133, J1.138, J1.139, J1.144, J1.145, J1.146, J1.149, J1.150, J1.155, J1.156, J1.161, J1.162, J1.165, J1.167, J1.168, J1.171, J1.172, J1.177, J1.178, J1.183, J1.184, J1.186, J1.187, J1.190, J1.193, J1.196, J2.A0, J2.A1, J2.A2, J2.A3, J2.B0, J2.B1, J2.B2, J2.B3, J2.C0, J2.C1, J2.C2, J2.C3, J3.5, J4.3, J4.5, J4.9, J5.5, J5.8, J6.0, J6.6, J6.B, J7.2, P2.2, P2.10, R2.1, R4.1, R5.2, R6.1, R7.1, R9.1, R11.1, R13.1, R16.1, R17.1, R19.2, R21.2, R22.2, R24.1, R28.2, R29.2, R31.2, R32.2, R34.2, R35.2, R38.2, R42.2, R46.2, R47.2, R48.2, R49.2, R55.2, R80.2, R81.2, R82.1, R93.2, R94.2, R95.2, R96.1, R97.2, R99.2, R101.1, R102.1, R103.1, R104.2, R112.2, SW1.2, U1.AA2, U1.AA9, U1.AA20, U1.AA27, U1.AC6, U1.AC9, U1.AC13, U1.AC16, U1.AC20, U1.AC23, U1.AF1, U1.AF28, U1.AG2, U1.AG5, U1.AG9, U1.AG13, U1.AG16, U1.AG20, U1.AG24, U1.AG27, U1.B2, U1.B5, U1.B9, U1.B12, U1.B13, U1.B16, U1.B20, U1.B24, U1.B27, U1.C1, U1.C28, U1.D3, U1.F6, U1.F9, U1.F13, U1.F16, U1.F20, U1.F23, U1.H2, U1.H9, U1.H20, U1.H27, U1.J2, U1.J11, U1.J18, U1.K6, U1.K10, U1.K12, U1.K14, U1.K16, U1.K18, U1.K20, U1.K23, U1.L9, U1.L11, U1.L13, U1.L15, U1.L17, U1.L19, U1.M10, U1.M12, U1.M14, U1.M16, U1.M18, U1.M20, U1.M22, U1.N2, U1.N6, U1.N9, U1.N11, U1.N13, U1.N15, U1.N17, U1.N19, U1.N22, U1.N23, U1.N27, U1.P10, U1.P12, U1.P14, U1.P16, U1.P18, U1.P20, U1.P22, U1.P23, U1.R9, U1.R11, U1.R13, U1.R15, U1.R17, U1.R19, U1.T2, U1.T6, U1.T10, U1.T12, U1.T14, U1.T16, U1.T18, U1.T20, U1.T23, U1.T27, U1.U9, U1.U11, U1.U13, U1.U15, U1.U17, U1.U19, U1.V10, U1.V12, U1.V14, U1.V16, U1.V18, U1.W6, U1.W11, U1.W13, U1.W15, U1.W17, U1.W19, U1.W23, U1.Y11, U1.Y18, U2.B11, U2.B13, U2.B14, U2.D12, U2.E13, U2.F6, U2.F7, U2.F8, U2.F9, U2.F12, U2.F13, U2.G6, U2.G7, U2.G8, U2.G9, U2.G12, U2.H6, U2.H7, U2.H8, U2.H9, U2.H13, U2.J6, U2.J7, U2.J8, U2.J9, U2.J13, U2.K12, U2.L12, U2.M12, U2.M13, U2.N13, U3.5, U3.41, U4.21, U5.2, U6.2, U7.3, U8.2, U8.5, U8.9, U9.1, U9.9, U10.2, U11.3, U11.4, U11.5, U11.17, U12.0, U12.8, U14.2, U18.4, U18.5, U19.2, U20.3, X2.2, X2.4, X3.2, X3.4
unnamed: C8.1, R19.1, R25.2, U10.4
unnamed: C9.1, R22.1, R26.2, U14.4
unnamed: C10.2, U4.2, X3.1
unnamed: C11.1, U4.1, X3.3
unnamed: C31.1, R27.1, U15.6
unnamed: C32.1, R30.1, U16.6
unnamed: C33.1, R33.1, U13.6
unnamed: C34.1, R36.1, U17.6
unnamed: C202.2, U3.7, X2.1
unnamed: C203.1, U3.6, X2.3
unnamed: C205.1, J3.1, R60.2, U19.5
unnamed: C241.1, U11.13
unnamed: C242.1, U11.9
unnamed: C243.1, U11.7
unnamed: C243.2, R94.1
unnamed: C249.1, R97.1, R98.2, U6.4
unnamed: D3.2, R31.1
unnamed: D4.2, R34.1
unnamed: J3.2, R61.2, U19.1
unnamed: J3.3, R59.2, R62.2, U19.3
unnamed: J6.1, R111.2
unnamed: J6.8, R110.2
unnamed: Q1.1, R64.2, R65.2
unnamed: Q1.3, R59.1
unnamed: R1.1, U1.AA17
unnamed: R2.2, U1.AB17
unnamed: R3.1, U1.AA22
unnamed: R4.2, U1.AB23
unnamed: R10.1, U1.F19
unnamed: R11.2, U1.E19
unnamed: R18.1, U2.L13
unnamed: R18.2, U2.L14
unnamed: R29.1, U15.1
unnamed: R32.1, U16.1
unnamed: R35.1, U13.1
unnamed: R37.2, SW1.1
unnamed: R38.1, U17.1
unnamed: R39.1, R40.2, U1.AC7
unnamed: R60.1, U3.14
unnamed: R61.1, U3.19
unnamed: R62.1, U3.20
unnamed: R64.1, U3.22
unnamed: R70.1, U4.19
unnamed: R71.1, U4.17
unnamed: R72.1, U4.16
unnamed: R73.1, U4.15
unnamed: R74.1, U4.13
unnamed: R75.1, U4.12
unnamed: R76.1, U4.9
unnamed: R77.1, U4.8
unnamed: R79.1, R80.1, U8.3
unnamed: R81.1, U8.4
unnamed: R92.1, R93.1, U11.6
unnamed: R95.1, U11.8
V1P1: C39.2, C121.1, C122.1, C123.1, C124.1, C125.1, C126.1, C127.1, C128.1, C129.1, C130.1, C131.1, C132.1, C133.1, C134.1, C135.1, C162.1, FB6.1, L8.2, R105.1, U2.A5, U2.A10, U2.B6, U2.B10, U2.C4, U2.D13, U2.E1, U2.F2, U2.K2, U2.K13, U2.L1, U2.N5, U2.N10, U2.P4, U2.P10, U12.4
V1P2: C38.1, C251.2, C4001.1, C4002.1, C4003.1, C4004.1, C4005.1, C4006.1, C4007.1, C4008.1, C4009.1, C4010.1, C4011.1, C4012.1, C4013.1, C4014.1, C4015.1, C4016.1, C4017.1, C4018.1, C4019.1, C4020.1, C4021.1, C4022.1, C4023.1, C4024.1, C4025.1, C4026.1, C4027.1, C4028.1, C4029.1, C4030.1, C4031.1, C4032.1, C4033.1, C4034.1, C4035.1, C4036.1, C4037.1, C4038.1, C4039.1, C4040.1, C4041.1, C4042.1, C4043.1, C4044.1, C4045.1, C4046.1, C4047.1, C4048.1, C4049.1, C4050.1, FB7.1, L7.1, R100.1, U1.K9, U1.K11, U1.K17, U1.K19, U1.L10, U1.L12, U1.L14, U1.L16, U1.L18, U1.M11, U1.M13, U1.M15, U1.M17, U1.M19, U1.N10, U1.N12, U1.N14, U1.N16, U1.N18, U1.N20, U1.P9, U1.P11, U1.P13, U1.P15, U1.P17, U1.P19, U1.R10, U1.R12, U1.R14, U1.R16, U1.R18, U1.R20, U1.T11, U1.T13, U1.T15, U1.T17, U1.T19, U1.U10, U1.U12, U1.U14, U1.U16, U1.U18, U1.V11, U1.V13, U1.V15, U1.V17, U1.V19, U1.W12, U1.W14, U1.W18
V1P8: C24.1, C25.1, C26.1, C27.1, C28.1, C29.1, C36.2, C41.1, C42.1, C43.1, C44.1, C45.1, C46.1, C47.1, C48.1, C49.1, C50.1, C51.1, C52.1, C53.1, C54.1, C55.1, C56.1, C57.1, C58.1, C59.1, C60.1, C61.1, C62.1, C63.1, C64.1, C65.1, C101.1, C102.1, C103.1, C104.1, C105.1, C106.1, C107.1, C108.1, C109.1, C110.1, C111.1, C112.1, C113.1, C114.1, C115.1, C116.1, C151.1, C152.1, C153.1, C154.1, C155.1, C156.1, C161.1, C180.1, C182.1, C184.1, C210.1, C211.1, C212.1, C213.1, C214.1, C215.1, C216.1, C217.1, C218.1, C219.1, C220.1, C221.1, C245.1, FB5.1, FB8.1, J1.81, J1.82, J1.87, J1.88, J1.95, J1.96, J1.103, J1.104, J1.111, J1.112, J1.117, J1.118, L6.2, R1.2, R3.2, R20.1, R40.1, R43.1, R44.1, R45.1, R92.2, U1.AA1, U1.AA11, U1.AA18, U1.AA28, U1.AB10, U1.AD6, U1.AD9, U1.AD13, U1.AD16, U1.AD20, U1.AD23, U1.AG1, U1.AG28, U1.AH2, U1.AH5, U1.AH9, U1.AH13, U1.AH16, U1.AH20, U1.AH24, U1.AH27, U1.B1, U1.H1, U1.K5, U1.K8, U1.N1, U1.N5, U1.T1, U1.T5, U1.T24, U1.T28, U1.U21, U1.W5, U1.W7, U1.W24, U1.Y16, U2.B2, U2.C3, U2.D4, U2.D7, U2.D8, U2.D9, U2.E4, U2.F4, U2.G4, U2.H4, U2.L4, U2.L5, U2.L7, U2.L8, U2.L9, U2.M3, U18.8
V2P5: C250.1, C4060.1, C4061.1, C4062.1, C4063.1, R98.1, U1.J8, U1.J21, U1.Y8, U1.Y21, U6.5
V3P3A: C12.1, C13.1, C16.1, C30.1, R14.1, R15.1, R26.1, U4.10, U4.11, U4.20, U14.5
V3P3D: C5.1, C17.1, C35.2, C160.1, C200.1, C201.1, D3.1, FB4.1, J1.199, J2.6, J4.1, J6.4, P2.4, Q1.2, R25.1, R27.2, R30.2, R36.2, R50.1, R51.1, R52.1, R53.1, R54.1, R57.1, R58.1, R65.1, R78.2, R83.2, R91.1, R106.1, R107.1, R108.1, R109.1, R110.1, R111.1, U3.8, U3.44, U10.5, U15.4, U16.4, U17.4, U18.1, U20.5
VALT_FE: D2.1, J2.1, J2.3, R28.1, U20.2
VALT_MB: D1.1, J7.1
VRAW: C6.1, C7.1, C37.1, C40.1, C240.1, C248.1, R33.2, U6.1, U8.7, U10.1, U10.3, U11.1, U11.2, U11.16, U12.3, U13.4, U14.1
VUSB: C231.1, FB1.2, R8.2, U8.6, U9.6, U9.7, U9.8

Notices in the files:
sw/fpga/main_board/diagnostic/diagnostic.qsf:
Copyright (C) 1991-2012 Altera Corporation
sw/fpga/targets/gige/gige.qsf:
Copyright (C) 1991-2014 Altera Corporation. All rights reserved.
hw/frontend/daisho_gige_fe/gige_fe.kicad_pcb:
Copyright © 2013 Benjamin Vernoux
License: GNU General Public License, version 2
hw/main_board/main_board.kicad_pcb:
Copyright © 2013 Jared Boone
